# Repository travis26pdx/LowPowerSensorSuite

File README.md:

# LowPowerSensorSuite
Repository for 2022 Capstone: 2nd Gen Low Power Environmental Sensor Suite

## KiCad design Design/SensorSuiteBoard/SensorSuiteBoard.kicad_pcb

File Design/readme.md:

These folders contain the design files including:
1. KiCad files
2. CAD file for base board

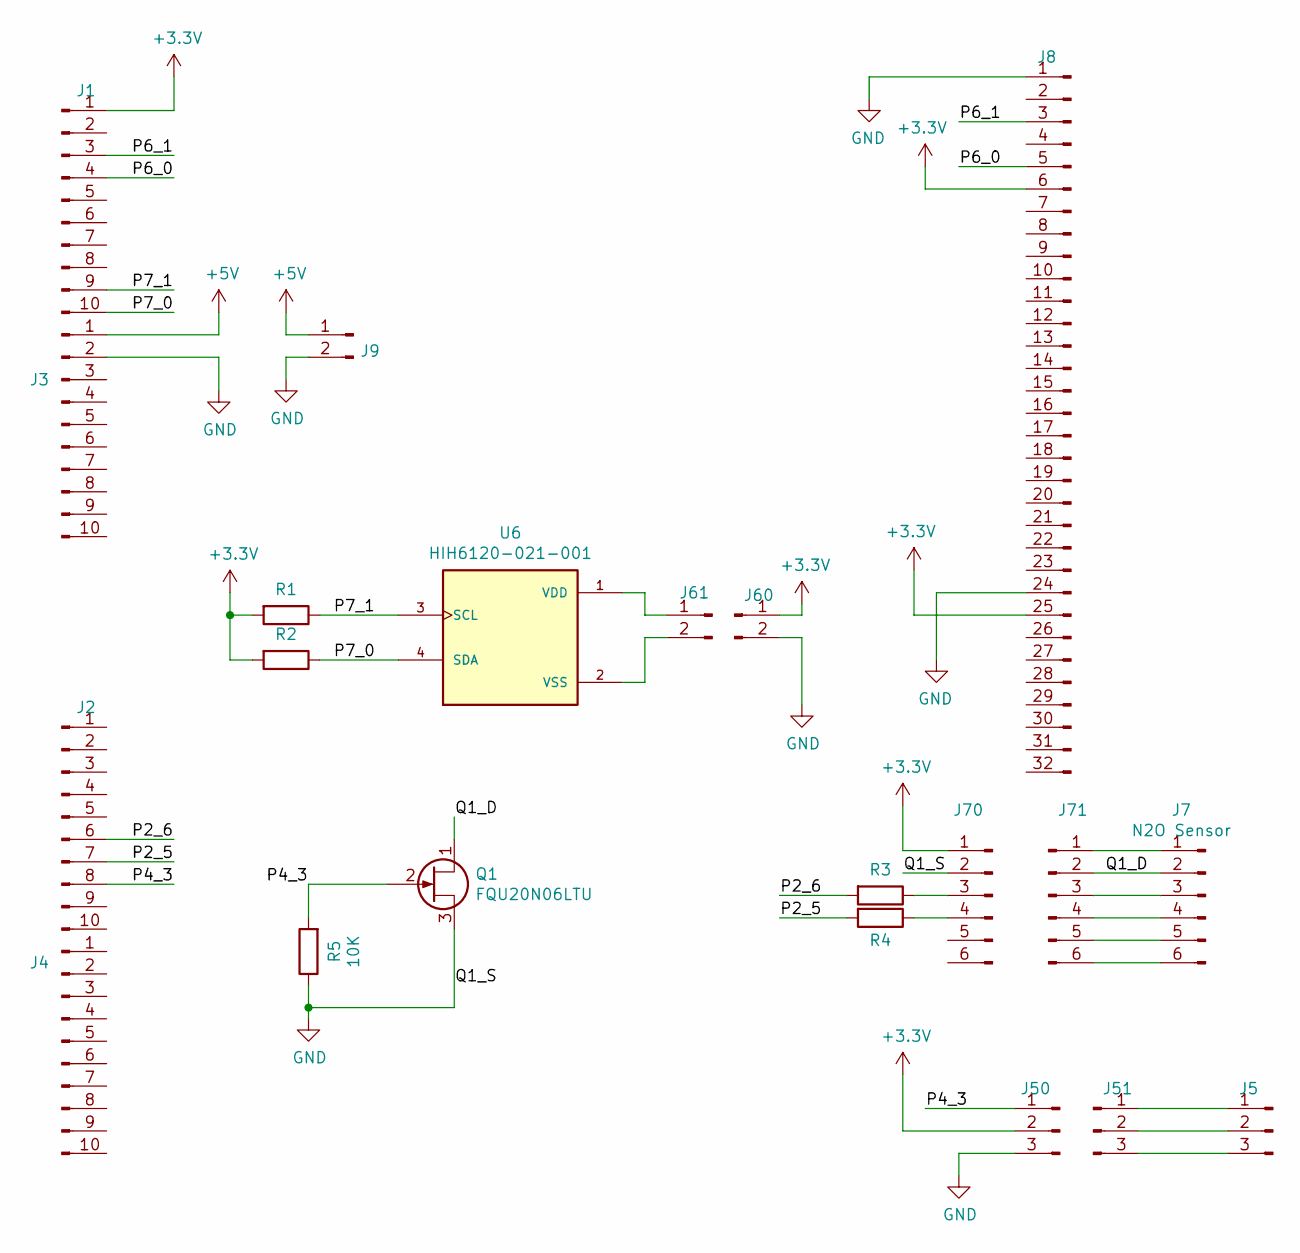
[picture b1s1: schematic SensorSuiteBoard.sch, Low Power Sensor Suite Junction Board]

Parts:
J1, J2, J3, J4: Conn_01x10_Male; Pin_Header_Straight_1x10_Pitch2.54mm
J5, J50, J51: Conn_01x03_Male; Pin_Header_Straight_1x03_Pitch2.54mm
J7: N2O Sensor; Pin_Header_Straight_2x03_Pitch2.54mm
J8: Conn_01x32_Male; Pin_Header_Straight_2x16_Pitch2.54mm
J9, J60, J61: Conn_01x02_Male; Pin_Header_Straight_1x02_Pitch2.54mm
J70, J71: N2O Sensor; Pin_Header_Straight_1x06_Pitch2.54mm
Q1: FQU20N06LTU
R1, R2, R3, R4: R; R_Box_L13.0mm_W4.0mm_P9.00mm
R5: 10K; R_Box_L13.0mm_W4.0mm_P9.00mm
U6: HIH6120-021-001; HIH8120_breakout

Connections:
+3V3: J1.1, J8.6, J8.25, J50.2, J60.1, J70.1, R1.2, R2.2
+5V: J3.1, J9.1
/P2_5: J2.7, R4.2
/P2_6: J2.6, R3.2
/P4_3: J2.8, J50.1, Q1.2 (G), R5.2
/P6_0: J1.4, J8.5
/P6_1: J1.3, J8.3
/P7_0: J1.10, R2.1, U6.4 (SDA)
/P7_1: J1.9, R1.1, U6.3 (SCL)
GND: J3.2, J8.1, J8.24, J9.2, J50.3, J60.2, J70.2, Q1.3 (S), R5.1
unnamed: J5.1, J51.1
unnamed: J5.2, J51.2
unnamed: J5.3, J51.3
unnamed: J7.1, J71.1
unnamed: J7.2, J71.2, Q1.1 (D)
unnamed: J7.3, J71.3
unnamed: J7.4, J71.4
unnamed: J7.5, J71.5
unnamed: J7.6, J71.6
unnamed: J61.1, U6.1 (VDD)
unnamed: J61.2, U6.2 (VSS)
unnamed: J70.3, R3.1
unnamed: J70.4, R4.1

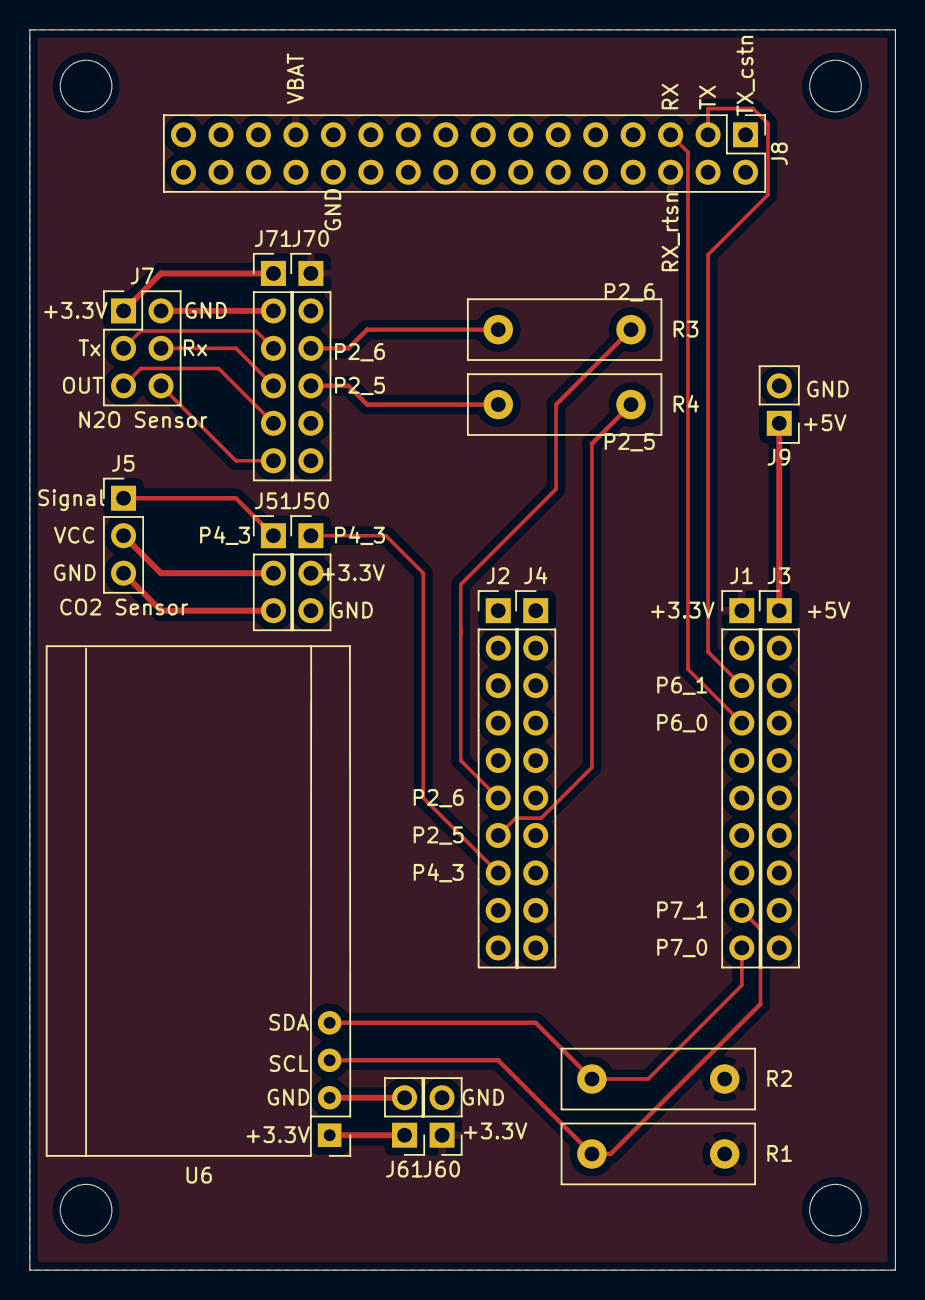
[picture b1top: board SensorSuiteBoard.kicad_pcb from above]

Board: 2 copper layers, 58.7 x 84.1 mm, 19 parts (0 on the bottom side), 23 nets.

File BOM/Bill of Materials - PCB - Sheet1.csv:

Bill of Materials: ,Team 13,Second Generation Low Power Environmental Sensor Suite,,,,,,,,
Last Modified:,6/8/2022,,,,,,,,,
Schematic version:,1.1,,,,,,,,,
PCB version:,1.00,,,,,,,,,
BOM revision:,1.00,,,,,,,,,
,,,,,,,,,,
Quantity,Part References,P/NP*,Mfg,Mfg PN,Description,Dist,Dist Part Number,Cost Ea.,Cost Total,URL
1,U1,P,Oshpark,N/A,Sensor Suite Junction Board,Osh Park,N/A,$20.00,$20.00,https://oshpark.com/
1,U6,P,Honeywell,HIH6120,SENS HUMI/TEMP 3.3V I2C 2% 4SIP,Digi-Key,480-5706-1-ND,$12.90,$12.90,https://www.digikey.com/en/products/detail/honeywell-sensing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
1,U5,P,Dynament,DS0002,NO2 Sensor,Dynament,DS0002,,$0.00,
105,"J1-J9, J50/J51,J60/J61,J70/J71",P,MCIGICM,N/A,Pin Headers,Amazon,N/A,$0.01,$1.31,https://www.amazon.com/MCIGICM-Header-2-45mm-Arduino-Connect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
2,"R1,R2",P,Yageo,RT1206BRD075KL,RES SMD 5K OHM 0.1% 1/4W 1206,Digi-Key,YAG5090CT-ND,$0.65,$1.30,https://www.digikey.com/en/products/detail/yageo/RT1206BRD07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
,,,,,,,,,,
,,,,,,,,Total:,$35.51,

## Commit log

2022-03-03 Create Readme.md
    Create SD Card folder and readme.md
2022-03-04 Add existing file
2022-03-20 Added endseek() function. Moves pointer to EOF
    After opening an existing file, use "jaffl.endseek()", and the pointer moves to EOF to append next printf
2022-03-22 REV 1
    Fixed tables and directory model. Note: NO2 button disfunctional for now.
2022-03-31 Add files via upload
    SD card code integrated into main code.
2022-03-31 REV 1
    Last year’s GUI required 10 data values to be in the log file to operate correctly, so I modified the GUI code to be able to work with 3 data values (temperature, humidity, N2O).
2022-03-31 REV 2
    Modified last year’s GUI to update the data table every time new data was stored into the log file so that live data could be read.
2022-03-31 REV 1
    InteractiveGraph class arguments had to be changed.
2022-03-31 REV 1
    Updated data.
2022-04-01 REV3
    All Buttons now work correctly. Increased size of graph to match fill in the space.
2022-04-02 REV4
    GUI now displays the seconds in the timestamps instead of just hours and minutes. GUI also now displays all of the dates from the log file where each date displayed on the GUI will span an amount equ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
2022-04-08 REV4
    Deleted date drop down menu, deleted span button, deleted time scroll bar. Deleted 0's from data table. Graph plots last 10 data values from the log file. Graphs are updated and display live data.
2022-04-22 Update SensorSuiteGUI.py
    Changing the table so that it only shows the last certain amount of values(10). Also, making it so that only the last date is displayed in the table.
2022-05-05 REV6
    The problem with this revision is that for some reason when the GUI is launched and there is less than 36 lines of data in the log file then the graph in the GUI will display N2O data only regardless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
2022-05-13 REV7
    Fixed GUI according to new sample rates as well as some other small bugs. GUI now displays last 100 pieces of data. Also, changed the null sensor values from 0 to 65535 in order to also account when 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
2022-05-13 REV1
    Changed the null sensor values from 0 to 65535 in order to also account when N2O sensor value 0. Temperature gets sampled every 1 minute, Humidity every 2 minutes, and N2O every 10 minutes.
2022-05-25 Create 1
2022-05-27 REV 2
    Added N2O code into the main code (warm up time for N2O sensor is 1 minute). Also added new SD card code into the main code, where millis() function will get stored in the SD card file.
2022-06-01 REV 3
    SD card log file name for N2O renamed to "N2O" from "NO2".
2022-06-10 Upload kicad files for junction board
2022-06-10 Upload kicad schematic for full system.
2022-06-10 Baseboard CAD image. in millimeters.
2022-06-10 upload BOMs
2022-06-10 Upload various images
2022-06-10 Updated improved executive summary.
